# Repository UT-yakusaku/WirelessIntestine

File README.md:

This is the code for a paper titiled "Wireless Recording and Autoencoder Denoising of Intestinal Activity in Freely Moving Rats"

# WirelessIntestine

In this repository, we have 3 main components used in our paper.

`kicad/` : PCB and BOM of a custom-made board  
`nrf/` : a custom-made firmware for microcontroller (nrf51822)  
`analysis/model_train.py`: codes for training the denoising autoencoder  

## Building a firmware for nrf51822

Building and flashing firmware were described in the Makefile routines.
Connect the debugger to the microcontroller via JTAG, then build and flash the program using:

```
cd nrf/
make . -B ./_build
make flash_softdevice
```

## Detailed description of methods

Below, detailed description of analysis methods utilized in paper.

## Locomotion index

Locomotion index was calculated by the video of behaving rats in their homecage, recorded at a resolution of 960 by 540 pixels squared at 30 frames per second. As an initial preprocessing step for analyzing rats’ locomotion, video frames were converted to grayscale, with frames extracted every 180 frames (downsampled). The differential between successive frames was employed to quantify the magnitude of locomotion at each temporal point. In calculating this specific differential, the variance between the luminance values in each pixel, ranging from 0 to 255, was computed for every frame and aggregated across the entire frame. These aggregated values were designated as the locomotion levels and interpreted as an index of the rat's activity at specific intervals.
Locomotion levels were measured throughout the entire recording period. Home cage provided a confined space, restricting the variety of locomotion. Given this limitation, we estimated that their movements under these experimental conditions could be classified into two distinct states: moving (behaving) and non-moving (immobile). A Gaussian mixture model (GMM) was used to classify these states and determine the threshold for the locomotion index.

## Calculation of alpha in power-law noises

Alpha (α) is a parameter of power-law noise that defines the slope of the spectrum. Specifically, α is determined by the following relationship:
Where f is the frequency and S(f) is the power spectral density (PSD) of the power-law noise,
S(f) ∝ f ^(-α)
This equation indicates that a higher α corresponds to a steeper spectral slope, while a lower α results in a flatter spectrum in the Fourier-transformed waveforms. 

For the analysis of intestinal movement signals, a Fourier transform was applied to the acquired signals and represented on a double-logarithmic graph (Figure 1C, 2D). The signal comprising 180,000 data points was limited within the frequency range up to 5 Hz resulting in 18,000 points, meticulously smoothed employing a third-order Savitzky-Golay filter with a window size of 51, as executed via the Python Scikit-learn library. For the analysis across both logarithmic graphs, the smoothed signal was resampled at uniformly distributed intervals with a scaling factor of 100.02 in the logarithmic domain to circumvent bias in the subsequent fitting procedure. This precaution addresses the intrinsic characteristic of data sampled in linear space, which predisposes it to contain more data points in high-frequency regions as opposed to the low-frequency areas, resulting in their disproportionate representation when analyzed on a logarithmic scale. The resampled signal to mitigate this biased representation was depicted on a logarithmic scale spanning from 5 × 10⁻⁴ to 5 Hz, and thereafter, it was meticulously fitted with a linear function utilizing the least-squares methodology. This linear fit was employed to estimate a robust baseline for evaluating the strength of intestinal movement and calculate the slope of baseline, interpreted as the alpha.

## Definition of Intestinal Events

The amplitude of intestinal movements was segmented into 10.24-second bins. These amplitudes were then classified into two states—containing or lacking intestinal activity—using a Gaussian mixture model (the number of components is set to 2). Intestinal events were defined as periods in which intestinal activity was present.

## Autoencoder construction and training

### Training datasets

The training data comprised scalograms derived from amplitude-modulated waves, representing pure intestinal movements, amalgamated with pink noise to simulate motion-induced disruptions. The pure signal was modeled as the product of a modulation sine wave (frequency: 0.01-0.2 Hz) and a carrier wave (frequency: 0.5-0.7 Hz), with its intensity and frequency, varied across training samples to introduce diversity. Pink noise, inversely proportional to frequency, was incorporated to emulate movement artifacts, with a 15-fold difference in noise intensity between high- and low-noise conditions. The model was trained with 100 artificial 2000-second waves. The model was engineered to receive the high-noise version of signals as input and produce the low-noise version as output. The dataset was split into training and validation groups at an 8:2 ratio.

### Data preprocessing

For preprocessing, signals were converted into scalograms utilizing a short-term Fourier transform (STFT) with a 10.24-second Hann window, providing a frequency resolution of 0.1 Hz. These scalograms, restricted to the 0.4–6.5 Hz range, were segmented into 655-second segments and resized into 64 × 64 matrices for input into the autoencoder.

### Model construction

The autoencoder architecture comprises three parts: the encoder, bottleneck, and decoder. The encoder first processes the input matrices through a 2D convolutional layer with 32 filters of size 3 × 3, followed by a 2 × 2 max-pooling layer, reducing the matrices to 32 × 32 × 32. A second convolutional layer with identical filter dimensions and another max-pooling layer further reduces the size to 64 × 16 × 16. A 2D convolutional operation is performed in the bottleneck layer, increasing the depth to 128 while maintaining the spatial dimensions.
In the decoder, two upsampling layers, each followed by a convolutional layer, sequentially doubled the spatial dimensions and reduced the depth, ultimately restoring the matrices to 32 × 64 × 64. The final convolutional layer employed a linear activation function to conform the output to the input dimensions.

### Training

The model was trained to utilize the Adam optimizer with a learning rate of 0.001 and mean squared error (MSE) as the loss function. The training was confined to 100 epochs, with the learning rate reduced by a factor of 0.1 after five epochs without improvement. If no improvement was observed after ten epochs, training was stopped early. All routines were implemented using Python TensorFlow and Keras libraries.

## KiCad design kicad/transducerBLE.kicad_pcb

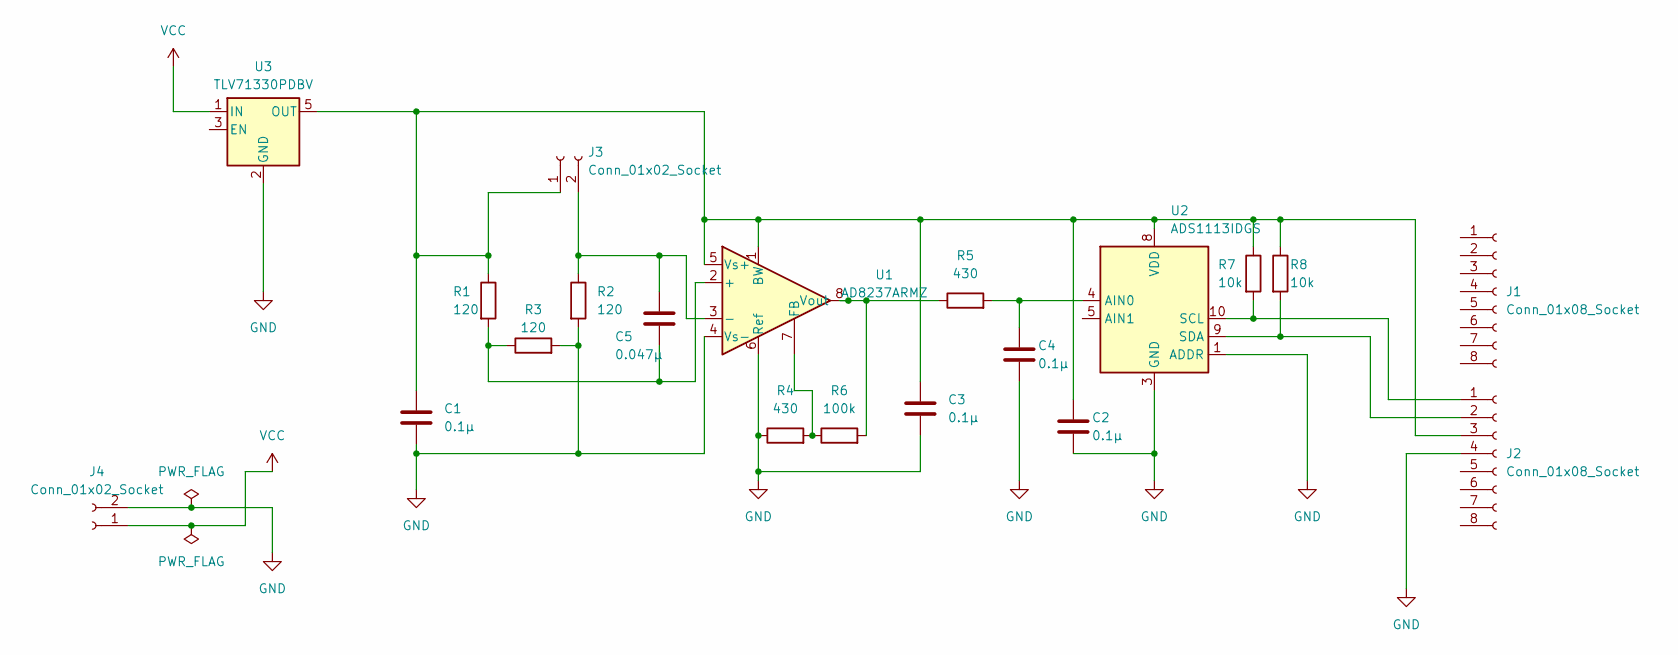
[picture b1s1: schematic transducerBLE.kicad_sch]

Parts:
C1, C2, C3, C4: 0.1µ; C_0402_1005Metric
C5: 0.047µ; C_1210_3225Metric
J1, J2: Conn_01x08_Socket; PinSocket_1x08_P2.54mm_Vertical
J3, J4: Conn_01x02_Socket; PinSocket_1x02_P2.00mm_Horizontal
R1, R2, R3: 120; R_0603_1608Metric
R4, R5: 430; R_0603_1608Metric
R6: 100k; R_0603_1608Metric
R7, R8: 10k; R_0402_1005Metric
U1: AD8237ARMZ; MSOP-8_3x3mm_P0.65mm
U2: ADS1113IDGS; TSSOP-10_3x3mm_P0.5mm
U3: TLV71330PDBV; SOT-23-5

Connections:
GND: C1.2, C2.2, C3.2, C4.2, J2.4, J4.2, R2.2, R3.2, R4.1, U1.4 (Vs-), U1.6 (Ref), U2.1 (ADDR), U2.3 (GND), U3.2 (GND)
unnamed: J2.1, R7.2, U2.10 (SCL)
unnamed: J2.2, R8.2, U2.9 (SDA)
unnamed: C1.1, C2.1, C3.1, J2.3, J3.1, R1.1, R7.1, R8.1, U1.1 (BW), U1.5 (Vs+), U2.8 (VDD), U3.5 (OUT)
unnamed: C5.1, J3.2, R2.1, U1.3 (-)
unnamed: C5.2, R1.2, R3.1, U1.2 (+)
unnamed: R4.2, R6.1, U1.7 (FB)
unnamed: R5.1, R6.2, U1.8 (Vout)
unnamed: C4.1, R5.2, U2.4 (AIN0)
VCC: J4.1, U3.1 (IN)

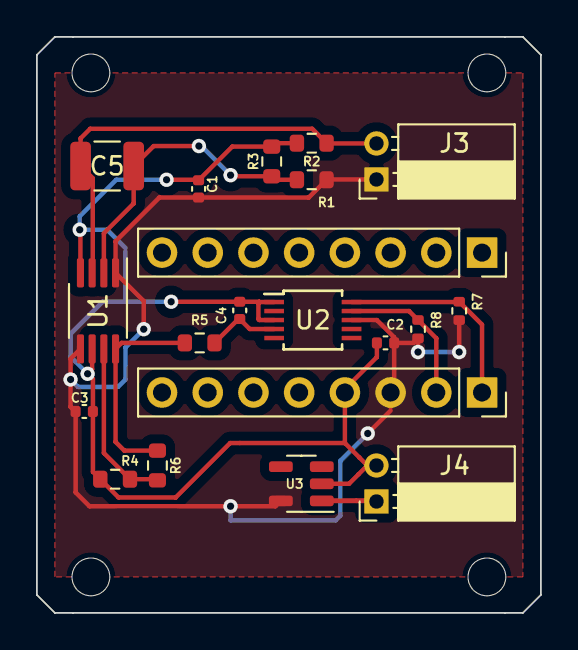
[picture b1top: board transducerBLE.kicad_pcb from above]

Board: 2 copper layers, 28.0 x 32.0 mm, 20 parts (0 on the bottom side), 10 nets.

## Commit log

2023-12-21 change main .ino name
2024-01-10 make env for nRF SDK example ble_app_uart
2024-01-10 impl ble uart send func
2024-01-10 modify makefile
2024-01-12 impl timer
2024-01-19 impl recv twi signals from sensor
2024-03-02 impl ble main loop
2024-07-24 impl bletest
2024-07-31 read twi within app timer handler
2024-08-13 impl ble data receiver
2024-08-13 impl recording system
2024-08-16 impl time counter
2024-10-02 fix unpack_sample.py for the new data format
2025-01-27 add codes for analysis
2025-01-27 add .gitignore
2025-01-27 change ADS1115 Channel 3 to 0
2025-01-27 add kicad pcb data for the custom-made measuring board
2025-03-02 add README.md
